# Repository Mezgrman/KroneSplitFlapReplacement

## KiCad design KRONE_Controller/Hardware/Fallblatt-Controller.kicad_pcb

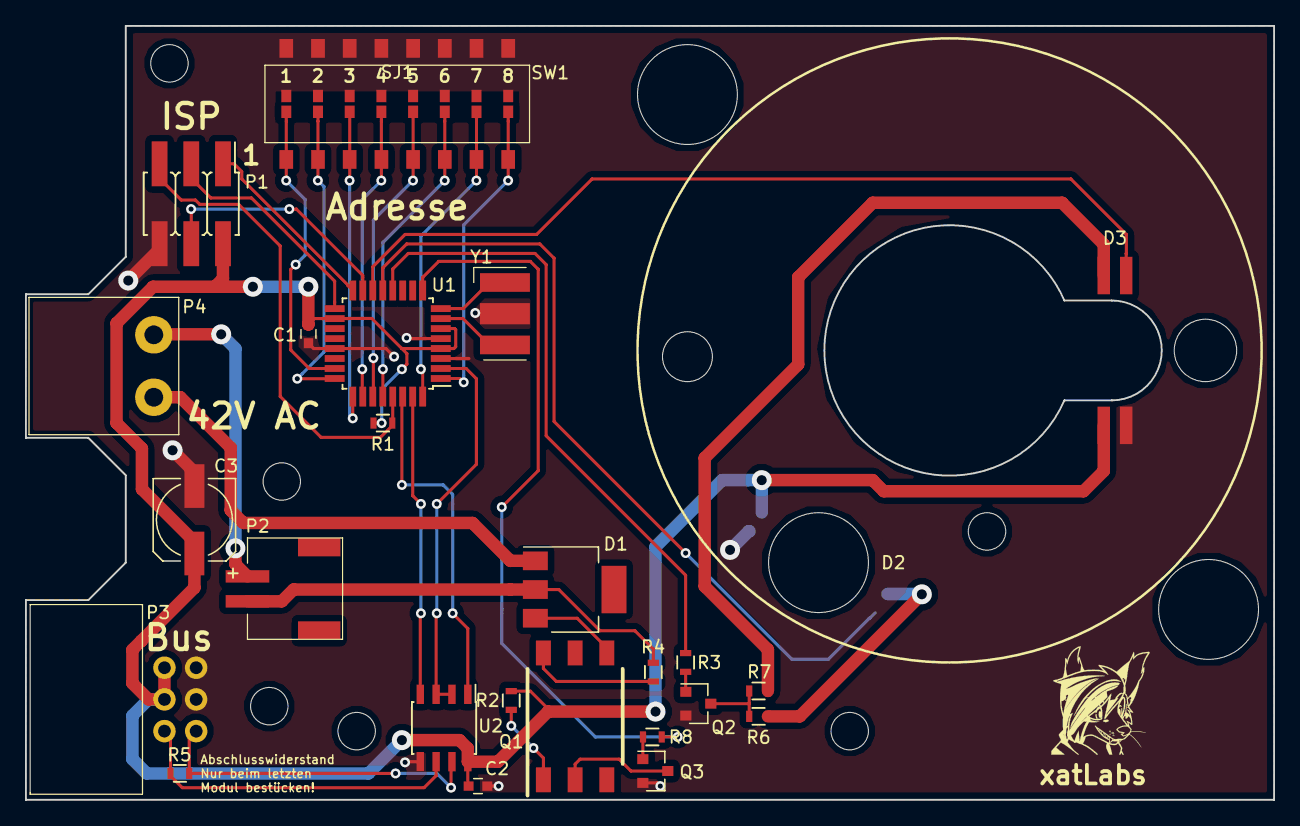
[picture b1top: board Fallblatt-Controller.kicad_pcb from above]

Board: 2 copper layers, 100.0 x 62.0 mm, 26 parts (1 on the bottom side), 37 nets.

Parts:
C1, C2: 100n; C_0603
C3: 47u; CP_Elec_6.3x5.3
D1: BT134W-600.135; SOT-223
D2: Nullposition; Photointerrupter_QRE1113_SMD_Across_Hole
D3: Impuls; Photointerrupter_QRE1113_SMD_Across_Hole_Mirrored
P1: ISP; Pin_Header_Straight_SMT_02x03
P2: Motor; NXW-02SMDK
P3: Interface; IDC_2x03_Angled
P4: 42V AC; AKL330-2
Q1: MOC3081M; Optocoupler_SMD_6pin
Q2, Q3: BC817-40; SOT-23
R1: 10k; R_0603
R2, R6, R7: 180R; R_0603
R3: 68R; R_0603
R4, R8: 4.7k; R_0603
R5: 150R; R_0603
SJ1: SolderBridge_x8_SMD
SW1: DM-08-V; SW_DIP_x8_SMD
U1: ATMEGA328P-AU; TQFP-32_7x7mm_Pitch0.8mm
U2: MAX485; SOIC-8_3.9x4.9mm_Pitch1.27mm
Y1: ZTTCC8.00MG; Resonator_ZTTCC_X.XX_MG

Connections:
+5V: C1.2, C2.2, C3.1, D2.1, D3.1, P1.2, P3.4, P3.6, R1.1, R2.2, U1.4, U1.6, U1.18, U2.8
GND: C1.1, C2.1, C3.2, D2.4, D3.4, P1.6, P3.3, P3.5, Q2.2, Q3.2, SJ1.9, SJ1.10, SJ1.11, SJ1.12, SJ1.13, SJ1.14, SJ1.15, SJ1.16, SW1.9, SW1.10, SW1.11, SW1.12, SW1.13, SW1.14, SW1.15, SW1.16, U1.3, U1.5, U1.21, U2.5, Y1.2
unnamed: D1.1, P4.2
unnamed: D1.2, P2.1, R3.1
unnamed: D1.3, Q1.4
unnamed: D2.2, R6.1
unnamed: D2.3, U1.13
unnamed: D3.2, R7.1
unnamed: D3.3, U1.14
unnamed: P1.1, U1.16
unnamed: P1.3, U1.17
unnamed: P1.4, U1.15
unnamed: P1.5, R1.2, U1.29
unnamed: P2.2, P4.1
unnamed: P3.1, R5.2, U2.7
unnamed: P3.2, R5.1, U2.6
unnamed: Q1.1, R2.1
unnamed: Q1.2, Q3.3
unnamed: Q1.6, R3.2
unnamed: Q2.1, R4.1
unnamed: Q2.3, R6.2, R7.2
unnamed: Q3.1, R8.1
unnamed: R4.2, U1.12
unnamed: R8.2, U1.9
unnamed: SJ1.1, SW1.1, U1.23
unnamed: SJ1.2, SW1.2, U1.24
unnamed: SJ1.3, SW1.3, U1.25
unnamed: SJ1.4, SW1.4, U1.26
unnamed: SJ1.5, SW1.5, U1.27
unnamed: SJ1.6, SW1.6, U1.28
unnamed: SJ1.7, SW1.7, U1.32
unnamed: SJ1.8, SW1.8, U1.1
unnamed: U1.2, U2.2, U2.3
unnamed: U1.7, Y1.3
unnamed: U1.8, Y1.1
unnamed: U1.30, U2.1
unnamed: U1.31, U2.4

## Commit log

2019-01-16 Updated splitflap controller schematic to new kicad version
2019-01-16 Some old hardware changes for v1.1
